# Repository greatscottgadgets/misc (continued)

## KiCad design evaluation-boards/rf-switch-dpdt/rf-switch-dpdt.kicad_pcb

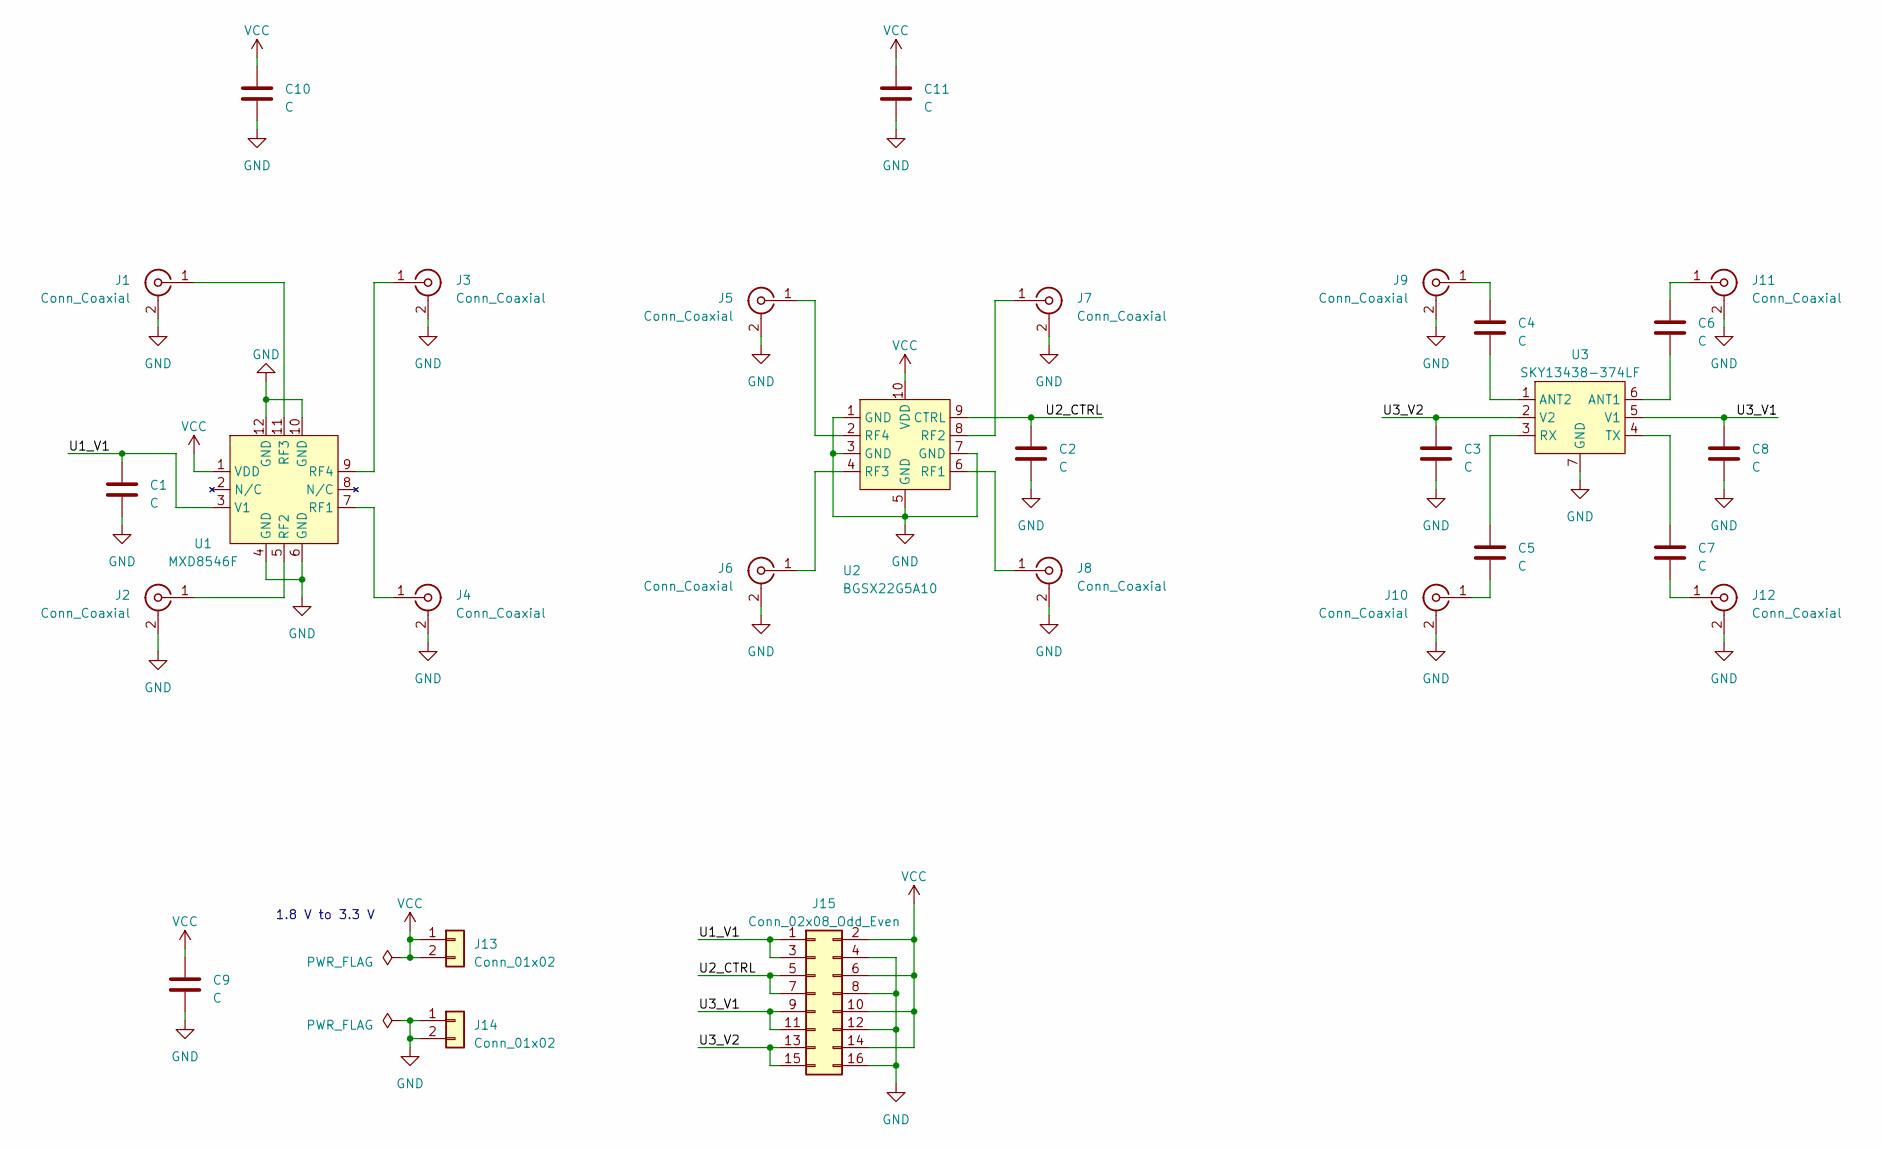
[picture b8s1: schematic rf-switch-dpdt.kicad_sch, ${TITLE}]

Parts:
C1, C2, C3, C4, C5, C6, C7, C8, C9, C10, C11: C; C_0402_1005Metric
J1, J2, J3, J4, J5, J6, J7, J8, J9, J10, J11, J12: Conn_Coaxial; CONSMA003.062
J13, J14: Conn_01x02; PinHeader_1x02_P2.54mm_Vertical
J15: Conn_02x08_Odd_Even; PinHeader_2x08_P2.54mm_Vertical
U1: MXD8546F; QFN-12-1EP_2x2mm_P0.5mm_EP1x1mm
U2: BGSX22G5A10; ATSLP-10-50
U3: SKY13438-374LF; Skyworks_SKY65404-31

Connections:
/U1_V1: C1.1, J15.1, J15.3, U1.3 (V1)
/U2_CTRL: C2.1, J15.5, J15.7, U2.9 (CTRL)
/U3_V1: C8.1, J15.9, J15.11, U3.5 (V1)
/U3_V2: C3.1, J15.13, J15.15, U3.2 (V2)
GND: C1.2, C2.2, C3.2, C8.2, C9.2, C10.2, C11.2, J1.2 (Ext), J2.2 (Ext), J3.2 (Ext), J4.2 (Ext), J5.2 (Ext), J6.2 (Ext), J7.2 (Ext), J8.2 (Ext), J9.2 (Ext), J10.2 (Ext), J11.2 (Ext), J12.2 (Ext), J14.1, J14.2, J15.4, J15.8, J15.12, J15.16, U1.4 (GND), U1.6 (GND), U1.10 (GND), U1.12 (GND), U1.13 (GND), U2.1 (GND), U2.3 (GND), U2.5 (GND), U2.7 (GND), U3.7 (GND)
unnamed: J1.1 (In), U1.11 (RF3)
unnamed: J2.1 (In), U1.5 (RF2)
unnamed: J3.1 (In), U1.9 (RF4)
unnamed: J4.1 (In), U1.7 (RF1)
unnamed: J5.1 (In), U2.2 (RF4)
unnamed: J6.1 (In), U2.4 (RF3)
unnamed: J7.1 (In), U2.8 (RF2)
unnamed: J8.1 (In), U2.6 (RF1)
unnamed: C4.1, J9.1 (In)
unnamed: C5.2, J10.1 (In)
unnamed: C6.1, J11.1 (In)
unnamed: C7.2, J12.1 (In)
unnamed: C6.2, U3.6 (ANT1)
unnamed: C4.2, U3.1 (ANT2)
unnamed: C5.1, U3.3 (RX)
unnamed: C7.1, U3.4 (TX)
VCC: C9.1, C10.1, C11.1, J13.1, J13.2, J15.2, J15.6, J15.10, J15.14, U1.1 (VDD), U2.10 (VDD)

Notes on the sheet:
1.8 V to 3.3 V

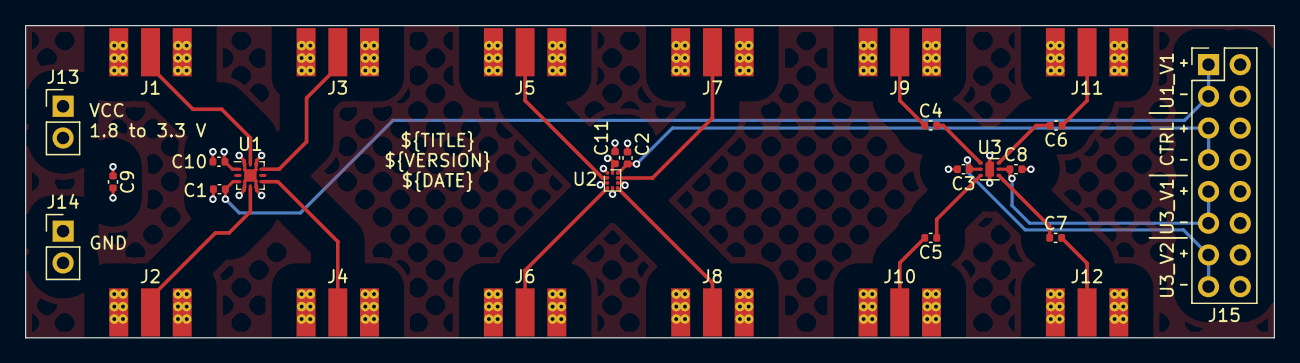
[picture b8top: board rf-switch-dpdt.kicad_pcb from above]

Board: 4 copper layers, 100.0 x 25.0 mm, 29 parts (0 on the bottom side), 22 nets.
